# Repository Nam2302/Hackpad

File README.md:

# Naman's Hackpad
The Hackpad has 8-inputs (7 switches + rotary encoder) with an OLED display. It uses [QMK](https://qmk.fm/) firmware, and the layout includes simple and frequently used shortcuts. 
<table align="center">
  <tr>
    <td></td>
    <td></td>
  </tr>
</table>

## PCB:
<table align="center">
  <tr>
    <td align="center"><strong>Schematic</strong></td>
    <td align="center"><strong>PCB</strong></td>
  </tr>
  <tr>
    <td></td>
    <td></td>
  </tr>
</table>
<p align="center">
  <strong>Made in KiCad</strong>
</p>

## Case:
The case has two pieces, which includes the top switch plate and a bottom container. Inside it is a cavity where the PCB sits. The design also has a distinct diagonal edge on the bottom.

<table align="center">
  <tr>
    <td></td>
    <td align="center"><strong>Top Case</strong></td>
  </tr>
  <tr>
    <td></td>
    <td align="center"><strong>PCB Case</strong></td>
  </tr>
  <tr>
    <td></td>
    <td align="center"><strong>Bottom Case</strong></td>
  </tr>
</table>
<p align="center">
  <strong>Made in Tinkercad</strong>
</p>

## Firmware
This Hackpad runs QMK firmware. There's a single layer with 7 keys mapped to the following shortcuts: new tab, new window, undo, redo, refresh, paste, and copy, with the encoder controlling volume. The OLED currently displays a simple status message.

## Final result:
This was the first PCB and CAD project I've ever finished, and had many challenges. I redesigned the PCB layout three separate times trying to get it under the 100x100mm size limit. 
The case design also had hurdles as I mostly started out eyeballing every measurement by dragging shapes around in Tinkercad, which never quite lined up right. I redid the whole thing once I actually found the align tool and coordinate input fields.
Finally, setting up Ubuntu to get the firmware going was a whole separate issue, but overall I am proud of my journey and final product.

## BOM:
Here is everything you need to create this Hackpad:
| Component | Amount |
| :--- | :---: |
| **Seeed XIAO RP2040** | 1x |
| **MX-Style switches (Cherry MX 1.00u)** | 7x |
| **1N4148 Diodes** | 7x |
| **EC11 Rotary encoder** | 1x |
| **0.91 inch OLED display** | 1x |
| **DSA keycaps** | 7x |
| **100nF Ceramic capacitor** | 1x |
| **M3x16mm screw** | 4x |
| **Case** (2 printed parts) | 1x |
| **PCB** | 1x |

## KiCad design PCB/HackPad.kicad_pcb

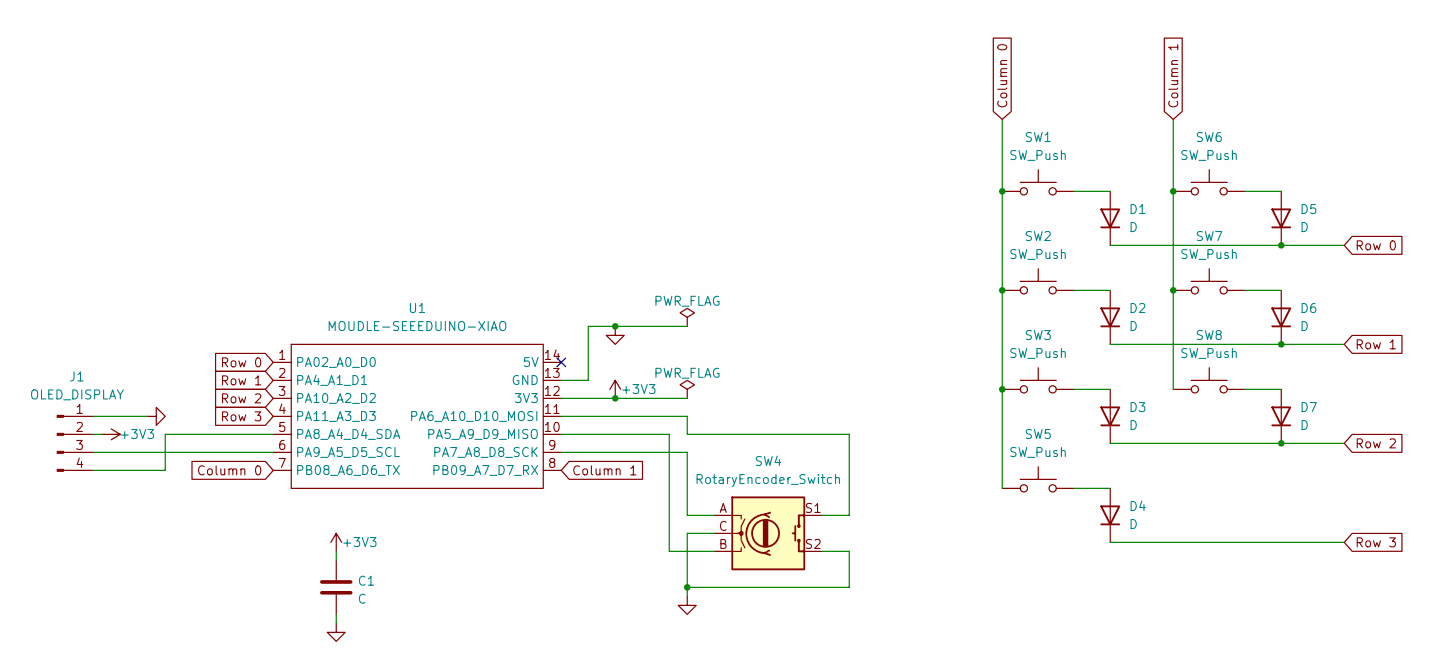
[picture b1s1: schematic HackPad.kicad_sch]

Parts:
C1: C; C_Disc_D3.0mm_W2.0mm_P2.50mm
D1, D2, D3, D4, D5, D6, D7: D; D_DO-35_SOD27_P7.62mm_Horizontal
J1: OLED_DISPLAY; SSD1306-0.91-OLED-4pin-128x32
SW1, SW2, SW3, SW5, SW6, SW7, SW8: SW_Push; SW_Cherry_MX_1.00u_PCB
SW4: RotaryEncoder_Switch; RotaryEncoder_Alps_EC11E-Switch_Vertical_H20mm
U1: MOUDLE-SEEEDUINO-XIAO; XIAO-Generic-Hybrid-14P-2.54-21X17.8MM

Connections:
+3V3: C1.1, J1.2, U1.12 (3V3)
Column 0: SW1.1, SW2.1, SW3.1, SW5.1, U1.7 (PB08_A6_D6_TX)
Column 1: SW6.1, SW7.1, SW8.1, U1.8 (PB09_A7_D7_RX)
GND: C1.2, J1.1, SW4.C, SW4.S2, U1.13 (GND)
unnamed: D1.2 (A), SW1.2
unnamed: D2.2 (A), SW2.2
unnamed: D3.2 (A), SW3.2
unnamed: D4.2 (A), SW5.2
unnamed: D5.2 (A), SW6.2
unnamed: D6.2 (A), SW7.2
unnamed: D7.2 (A), SW8.2
unnamed: J1.3, U1.6 (PA9_A5_D5_SCL)
unnamed: J1.4, U1.5 (PA8_A4_D4_SDA)
unnamed: SW4.B, U1.10 (PA5_A9_D9_MISO)
unnamed: SW4.S1, U1.11 (PA6_A10_D10_MOSI)
unnamed: SW4.A, U1.9 (PA7_A8_D8_SCK)
Row 0: D1.1 (K), D5.1 (K), U1.1 (PA02_A0_D0)
Row 1: D2.1 (K), D6.1 (K), U1.2 (PA4_A1_D1)
Row 2: D3.1 (K), D7.1 (K), U1.3 (PA10_A2_D2)
Row 3: D4.1 (K), U1.4 (PA11_A3_D3)

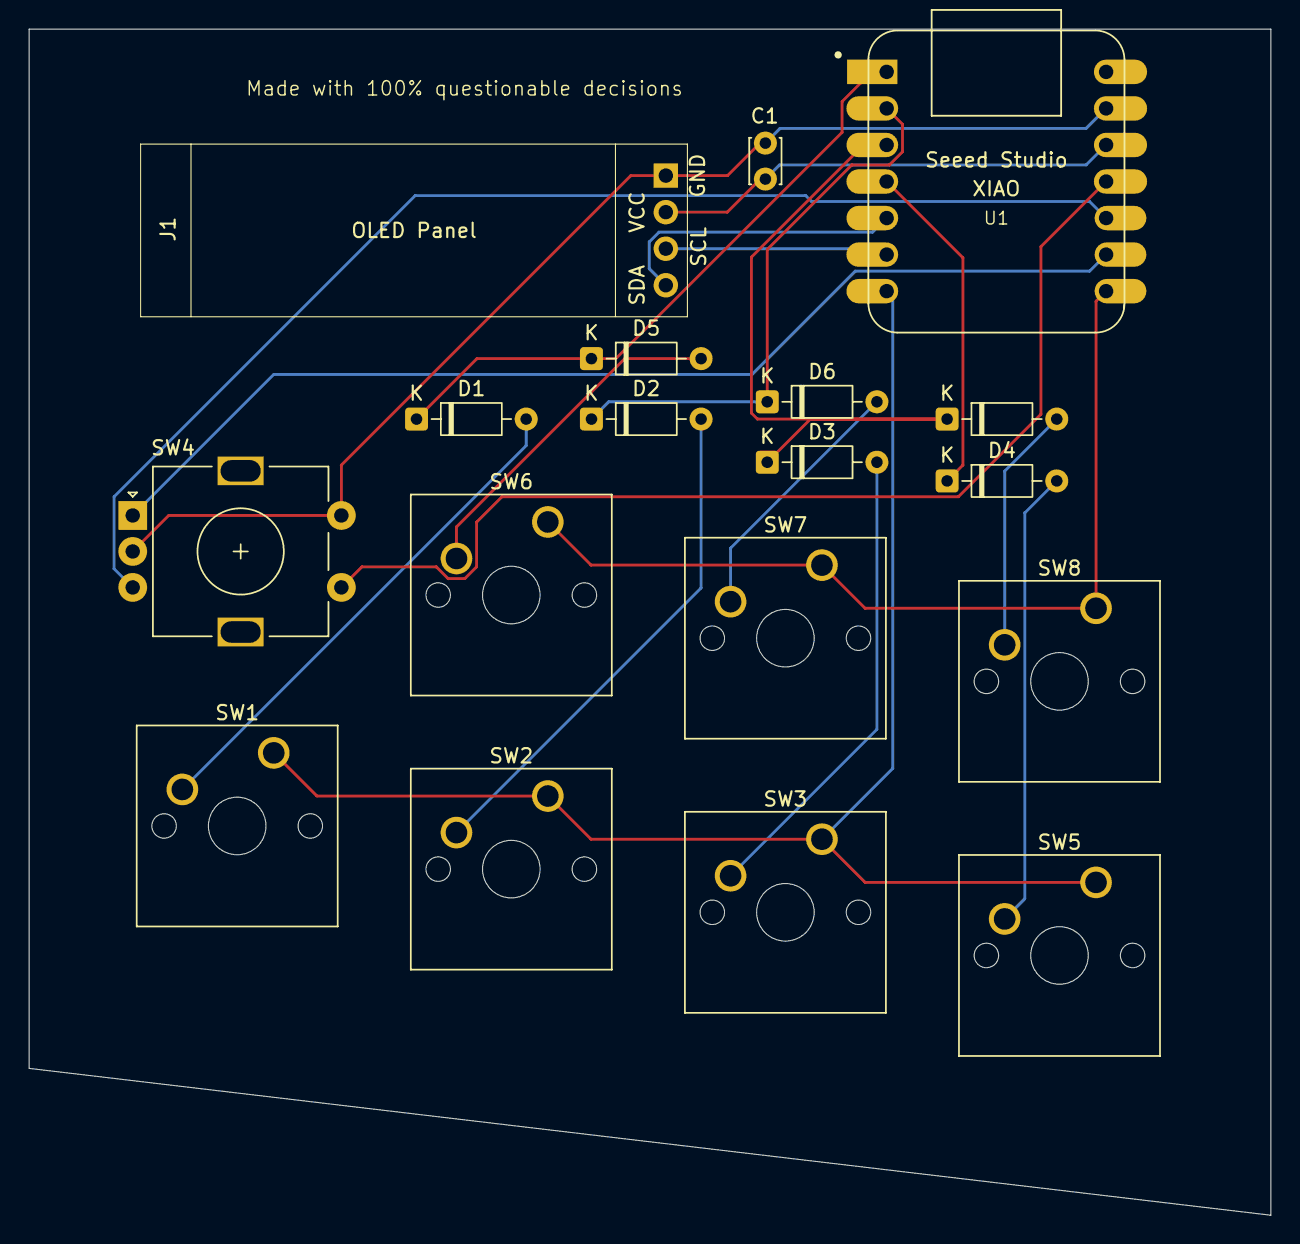
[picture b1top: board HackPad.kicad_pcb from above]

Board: 2 copper layers, 86.3 x 82.4 mm, 18 parts (0 on the bottom side), 20 nets.
